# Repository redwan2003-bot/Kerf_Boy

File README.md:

<h1 align="center">Kerf_Boy</h1>
<p align="center"><b>A module-based wearable electronics carrier, rebuilt from CHIP-BOY Mk III references for EasyEDA Pro.</b></p>
<p align="center">Kerf project by Redwan Ahmmed · Target CAD: EasyEDA Pro · Status: engineering reconstruction</p>

## What is it?

Kerf_Boy is a carrier-PCB redesign for a wrist-mounted device built around the Seeed Studio XIAO ESP32-S3 Sense. The source design combines an OLED, motion/environment/distance sensors, GPS, DFPlayer audio, buttons, a rotary encoder, illumination and battery monitoring.

The requirement is to **retain the original through-hole components and plug-in modules**, while improving the carrier circuitry and routing. This repository preserves source evidence, reconstructed footprints, mechanical references, verification results and the remaining design work.

> **Not ready to manufacture.** All 40 component footprints and native schematic bindings have been digitally checked. Exact-part qualification, circuit design, routing and prototype validation remain unfinished. The review board contains no routed circuit. See [production readiness](docs/PRODUCTION_READINESS.md).

## Start here

- [Latest GP7/navigation verification report](docs/reports/gp7-navigation-checkpoint.md)
- [Latest saved EasyEDA project](hardware/easyeda/qualification-fixes/native-gp7-navigation-review.epro2)

- [Latest manufacturer qualification report](docs/reports/part-qualification-review.md)
- [Current EasyEDA archive and corrected encoder](hardware/easyeda/qualification/README.md)

- [Latest Step 3 component and binding report](docs/reports/step-3-component-binding-report.md)
- [Hardware and footprint guide](hardware/README.md)
- [Complete reconstruction report (PDF)](docs/reports/complete-reconstruction-report.pdf)
- [Production readiness and unresolved work](docs/PRODUCTION_READINESS.md)
- [Verification and reproduction](docs/VERIFICATION.md)
- [Source provenance and licensing scope](docs/PROVENANCE.md)
- [Change history](CHANGELOG.md)

## Features being preserved

| Area | Original design requirement |
|---|---|
| Controller | XIAO ESP32-S3 Sense with camera, microphone and microSD |
| Display | Original 1.3-inch 128 x 64 OLED interface |
| Sensors | Original BNO055, BME280 and TOF400C module interfaces |
| Navigation | GPS module, rotary encoder, buttons and navigation switch |
| Audio | DFPlayer, speaker connection and buzzer function |
| Power and outputs | Single-cell battery concept, battery sensing, three LEDs and laser interface |

These describe the intended system, not tested capabilities of this rebuild. Exact part identities and unresolved electrical interfaces are tracked in the report.

## Repository layout

```text
Kerf_Boy/
├── README.md
├── AGENTS.md                 # Design constraints and future push workflow
├── CHANGELOG.md
├── hardware/
│   ├── README.md
│   ├── reference/original/   # Immutable supplied design evidence (50 files)
│   ├── reconstruction/       # Review boards, libraries, pin maps and checks
│   └── easyeda/              # Native-project status and conversion instructions
├── mechanical/               # Geometry guide and references to recovered DXFs
├── firmware/                 # Firmware status and required integration work
├── docs/
│   ├── PRODUCTION_READINESS.md
│   ├── VERIFICATION.md
│   ├── PROVENANCE.md
│   ├── ORDERING.md
│   ├── reports/              # Full report and historical engineering records
│   ├── images/               # Mechanical and hole-map previews
│   └── history/              # Explicitly superseded research
└── scripts/                  # Portable recovery and verification tools
```

## Verified reconstruction at a glance

| Item | Current evidence |
|---|---|
| Reference envelope | 92.710 x 63.500 mm |
| Original copper layers | Four: top, internal GND, internal 3V3, bottom |
| Review board | Two-layer geometry carrier only; no traces/netlist |
| Source files | 50 originals preserved with SHA-256 fingerprints |
| Component library | 40 footprints in the current EasyEDA review; historical 24-group evidence retained |
| Component/locator features | 138 round holes and two plated routed slots |
| Additional small holes | 51 via candidates, outside component footprints |
| Current bindings | 179 electrical pins/pads, 40 symbols/footprints; full circuit equivalence unverified |
| Independent geometry read-back | Passed at 0.000002 mm comparison tolerance |
| EasyEDA review | Complete component import and binding sheet saved; embedded libraries independently checked |
| Binding-review DRC / hardware test | 0 fatal, 0 errors, 1 shield-pin warning / physical test not performed |

## Review locally

```sh
git clone https://github.com/redwan2003-bot/Kerf_Boy.git
cd Kerf_Boy
python scripts/verify_repository.py
```

Open `hardware/reconstruction/complete-geometry-review.kicad_pcb` for positional review, or follow [EasyEDA status and import notes](hardware/easyeda/README.md). This is an intermediate CAD artifact, not a completed EasyEDA design. See [verification instructions](docs/VERIFICATION.md) for optional geometry regeneration.

## Project status

- [x] Source audit and digital mechanical-reference checks
- [x] Through-hole geometry recovery and independent CAD read-back
- [x] Reconstruction report and structured repository
- [x] Reconstruct and check 40 footprint bindings and 179 pin/pad matches in saved EasyEDA archive
- [ ] Finish exact-part qualification, body/courtyard geometry and physical fit checks
- [ ] Finalize power and GPIO architecture, including microSD conflicts
- [ ] Complete schematic, layout, routing and meaningful ERC/DRC
- [ ] Verify manufacturing exports and test a physical prototype

## Credits and license

The supplied CHIP-BOY Mk III schematic credits Victor Ranulfo Molina. Original material is kept as reference with its original markings. Repository organization follows [Kerf_Keeb](https://github.com/redwan2003-bot/Kerf_Keeb). See [LICENSE](LICENSE) and [provenance](docs/PROVENANCE.md); the repository license does not establish ownership of third-party source material.

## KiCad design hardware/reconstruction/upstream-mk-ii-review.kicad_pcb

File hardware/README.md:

# Latest component review

The [current EasyEDA component review](easyeda/step3-numbered/README.md) contains 40 reconstructed footprints and 179 verified symbol-to-pad bindings. The earlier 24-group and held-map files below remain historical evidence. Body/courtyard completion, ratings, physical qualification and circuit design remain open.

# Hardware

The target deliverable is an EasyEDA Pro carrier PCB using the original modules. This folder currently contains source evidence and an intermediate reconstruction, not a production design.

## Source versus reconstruction

- [reference/original](reference/original/): 50 supplied source files, preserved byte-for-byte. Original Gerbers describe the old design; they are not redesign manufacturing files.
- [reconstruction](reconstruction/): recovered geometry, review boards, measurements and mappings.
- [easyeda](easyeda/): status of the native EasyEDA project.

## Which library should I open?

| Path under reconstruction/ | Purpose |
|---|---|
| OriginalCarrier.pretty/ | 11 reconstructed interfaces, 85 mapped pads. Mapping is reconstructed, not native-netlist-certified. |
| UnresolvedOriginal.pretty/ | 13 reference groups with unresolved electrical identity. HOLD names and hole IDs are intentional. |
| original-interface-review.kicad_pcb | The 11 mapped groups at original locations. |
| complete-geometry-review.kicad_pcb | All 24 groups at original locations, including held groups. |
| reconstructed-pin-map.csv | Pad-by-pad source coordinates, drill sizes, shapes and function labels. |
| remaining-footprint-checks.json | Outstanding mapping issues and held features. |
| independent-footprint-verification.json | Recorded independent CAD read-back result. |

All original hole positions, pitches and drilling geometry are retained in the reconstructed groups. Footprints currently contain pad geometry and identification text; body outlines, courtyards, 3D models and symbol bindings are incomplete.

## Important distinctions

The original design has four copper layers. The review boards use two copper layers solely to carry geometry, contain no electrical nets/tracks, and must not be ordered as PCBs. The original SMD navigation switch's two locating holes are represented; its electrical SMD pads are not yet reconstructed.

[Readiness](../docs/PRODUCTION_READINESS.md) · [Verification](../docs/VERIFICATION.md) · [Report](../docs/reports/complete-reconstruction-report.pdf)

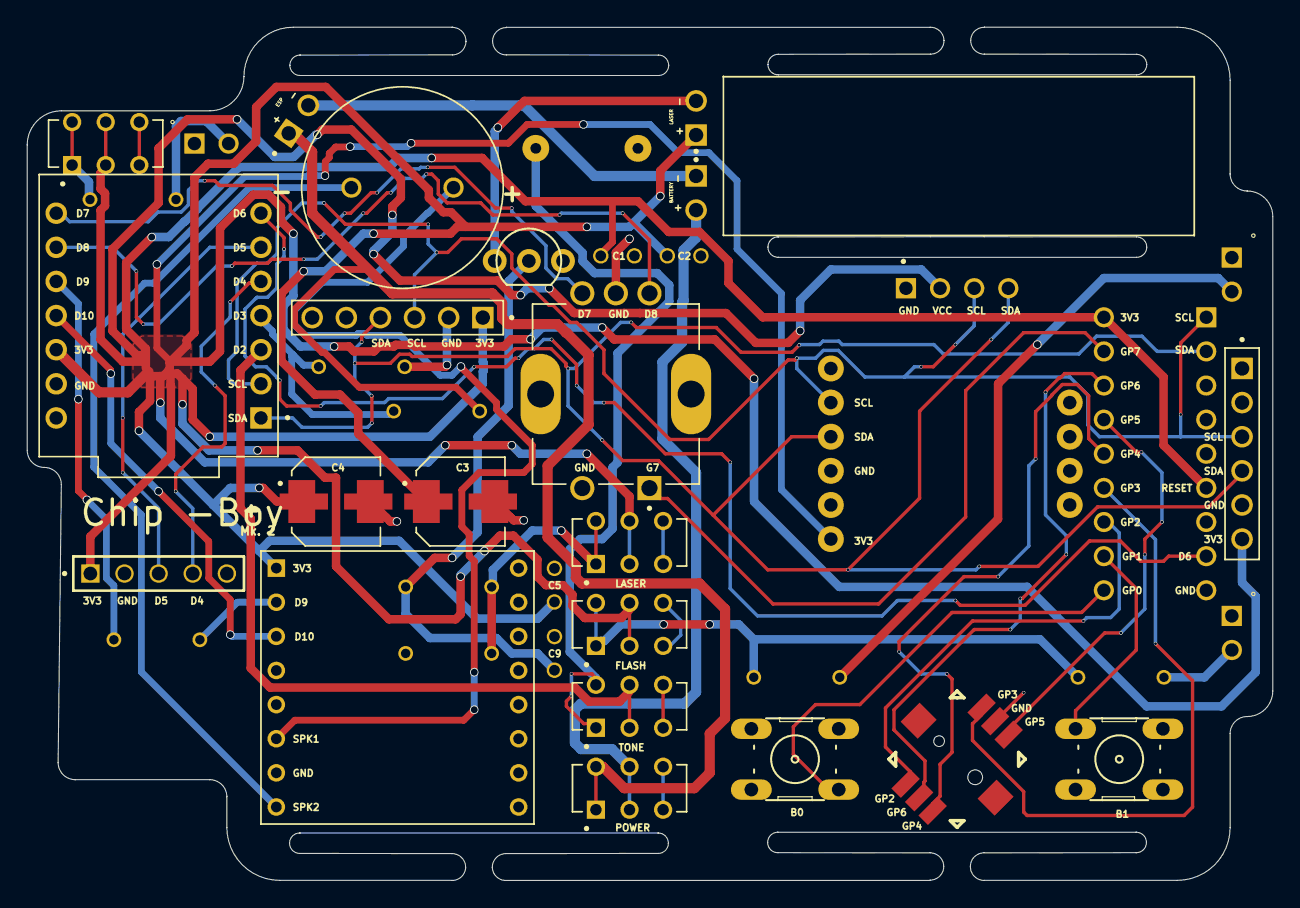
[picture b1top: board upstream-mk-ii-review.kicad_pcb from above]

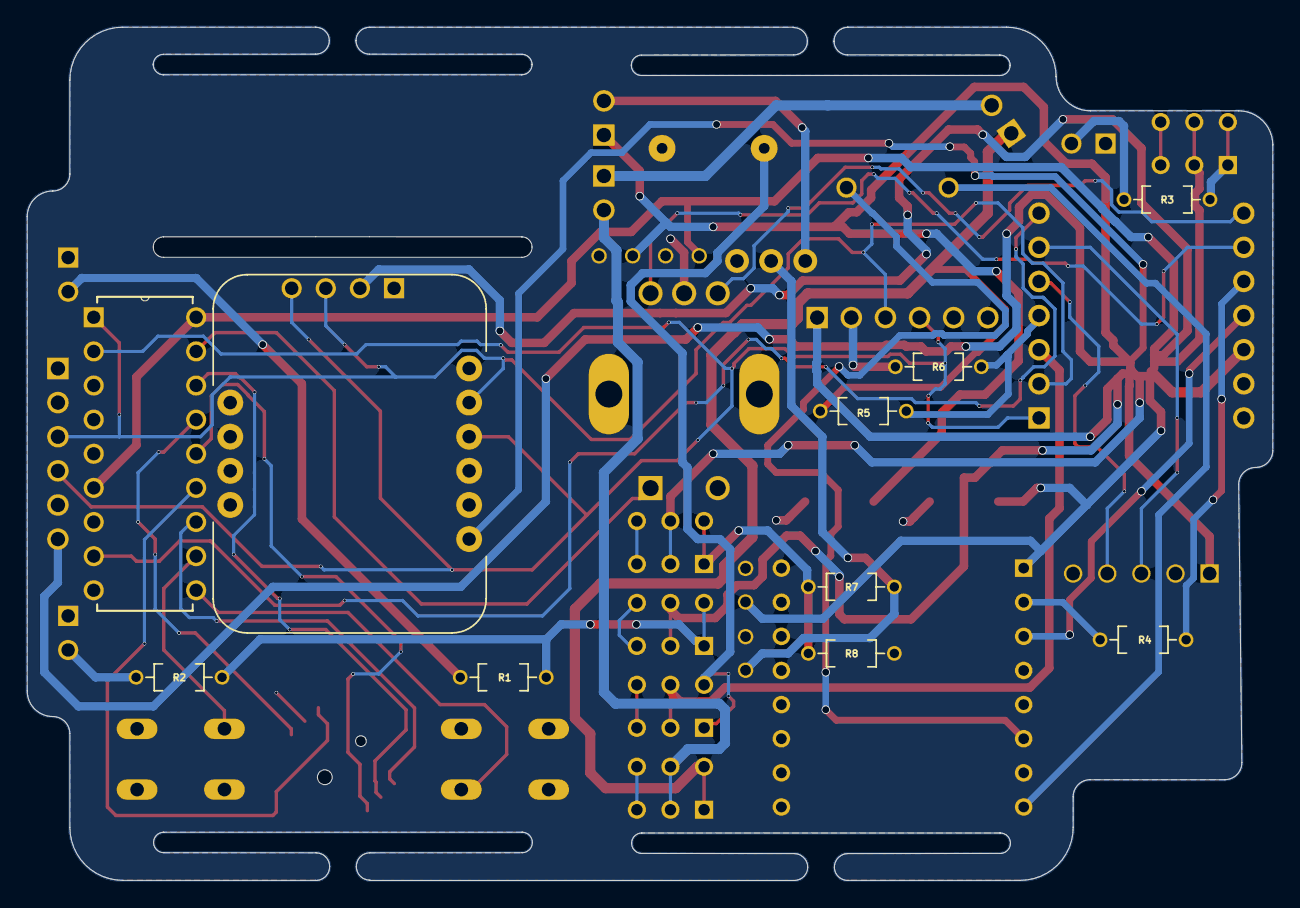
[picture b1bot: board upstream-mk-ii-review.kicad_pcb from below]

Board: 2 copper layers, 92.7 x 63.5 mm, 40 parts (10 on the bottom side), 41 nets.

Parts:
B0, B1: SKHHANA010; SW_SKHHANA010
BAT +/-: 2_pin_header; HARWIN_M20-9990246
BME: PPTC061LFBNRC; SULLINS_PPTC061LFBN-RC
BNO: BNO055; MODULE_2472
C1, C2, C5, C9: 0_1uF100V_CAP_FA14X7R2A104KNU00; CAPRB250W50L450T300H550
C3, C4: 47uF_SMD; CAP_EEETPV470XAV
CAM FLASH: switch top actuated; SW_MHSS1104
D1, D2, D3: led_through_hole; LED_WP7113ID
DF PLAYER: DFPLAYER; MODULE_DFR0299
ENCODER: rotary encoder; XDCR_PEC12R-4217F-S0024
ESP: xiao_esp32; MODULE_113991254
ESP +/-: 2_pin_header; HARWIN_M20-9990246
FLASH SW: switch top actuated; SW_MHSS1104
GPS: 5 pin header; SAMTEC_MTSW-105-07-L-S-240-LL
LASER: 2_pin_header; HARWIN_M20-9990246
LASER SW: switch top actuated; SW_MHSS1104
MCP: gpio extender; DIP254P762X533-18
MOSFET: mosfet; TO92
NAV: nav switch; SW_JS1400BFQ
OLED: DM-OLED096-636; MODULE_DM-OLED096-636
POWER SW: switch top actuated; SW_MHSS1104
R1, R2, R3, R4, R5, R6, R7, R8: resistor_through_hole; RESAD640W45L370D200
SPK: 15mm speaker; SPKR_CVS-1508
TOF Sensor: PPTC061LFBNRC; SULLINS_PPTC061LFBN-RC
TONE: Buzzer_3V; CUI_CMI-1295IC-0385T
TONE SW: switch top actuated; SW_MHSS1104

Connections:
GND: B0.3, B1.3, BME.2, BNO.3, BNO.7, C1.2, C2.2, C3.2, C4.2, C5.2, C9.1, D1.C, D2.C, D3.C, DF PLAYER.7, ENCODER.2, ENCODER.C, ESP.13, GPS.02, MCP.3, MCP.4, MCP.5, MCP.9, MOSFET.3, NAV.5, OLED.1, R6.1, R8.2, TOF Sensor.5, TONE.P
NetB0_1: B0.1, MCP.10
NetB1_1: B1.1, MCP.11
NetBAT +/-_1: BAT +/-.1, ESP +/-.2
NetBAT +/-_2: BAT +/-.2, POWER SW.3, POWER SW.4
NetBME_1: BME.1, BNO.1, C1.1, C2.1, C3.1, C4.1, C5.1, CAM FLASH.3, CAM FLASH.4, DF PLAYER.1, ESP.12, FLASH SW.3, FLASH SW.4, GPS.01, LASER.1, LASER SW.3, LASER SW.4, MCP.6, MCP.18, OLED.2, TOF Sensor.6
NetBME_3: BME.3, BNO.5, ESP.2, MCP.1, OLED.3, TOF Sensor.3
NetBME_4: BME.4, BNO.4, ESP.1, MCP.2, OLED.4, TOF Sensor.4
NetC9_2: C9.2, MOSFET.2, R7.1
NetCAM FLASH_1: CAM FLASH.1, CAM FLASH.2, R3.1
NetCAM FLASH_5: CAM FLASH.5, CAM FLASH.6
NetD1_A: D1.A, R1.2
NetD2_A: D2.A, R2.2
NetD3_A: D3.A, R3.2
NetDF PLAYER_2: DF PLAYER.2, R4.1
NetDF PLAYER_3: DF PLAYER.3, ESP.11
NetDF PLAYER_6: DF PLAYER.6, SPK.P
NetDF PLAYER_8: DF PLAYER.8, SPK.M
NetENCODER_1: ENCODER.1, MCP.17
NetENCODER_A: ENCODER.A, ESP.9
NetENCODER_B: ENCODER.B, ESP.8
NetESP +/-_1: ESP +/-.1, POWER SW.1, POWER SW.2, R5.2
NetESP_3: ESP.3, TONE SW.3, TONE SW.4
NetESP_4: ESP.4, R5.1, R6.2
NetESP_5: ESP.5, GPS.04
NetESP_6: ESP.6, GPS.03
NetESP_7: ESP.7, MCP.8
NetESP_10: ESP.10, R4.2
NetFLASH SW_1: FLASH SW.1, FLASH SW.2, R1.1, R2.1
NetFLASH SW_5: FLASH SW.5, FLASH SW.6
NetLASER SW_1: LASER SW.1, LASER SW.2, R7.2, R8.1
NetLASER SW_5: LASER SW.5, LASER SW.6
NetLASER_2: LASER.2, MOSFET.1
NetMCP_12: MCP.12, NAV.1
NetMCP_13: MCP.13, NAV.4
NetMCP_14: MCP.14, NAV.3
NetMCP_15: MCP.15, NAV.6
NetMCP_16: MCP.16, NAV.2
NetPOWER SW_5: POWER SW.5, POWER SW.6
NetTONE SW_1: TONE.N, TONE SW.1, TONE SW.2
NetTONE SW_5: TONE SW.5, TONE SW.6
